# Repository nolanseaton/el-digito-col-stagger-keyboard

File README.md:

# El Digito - Col Stagger PCB and Case

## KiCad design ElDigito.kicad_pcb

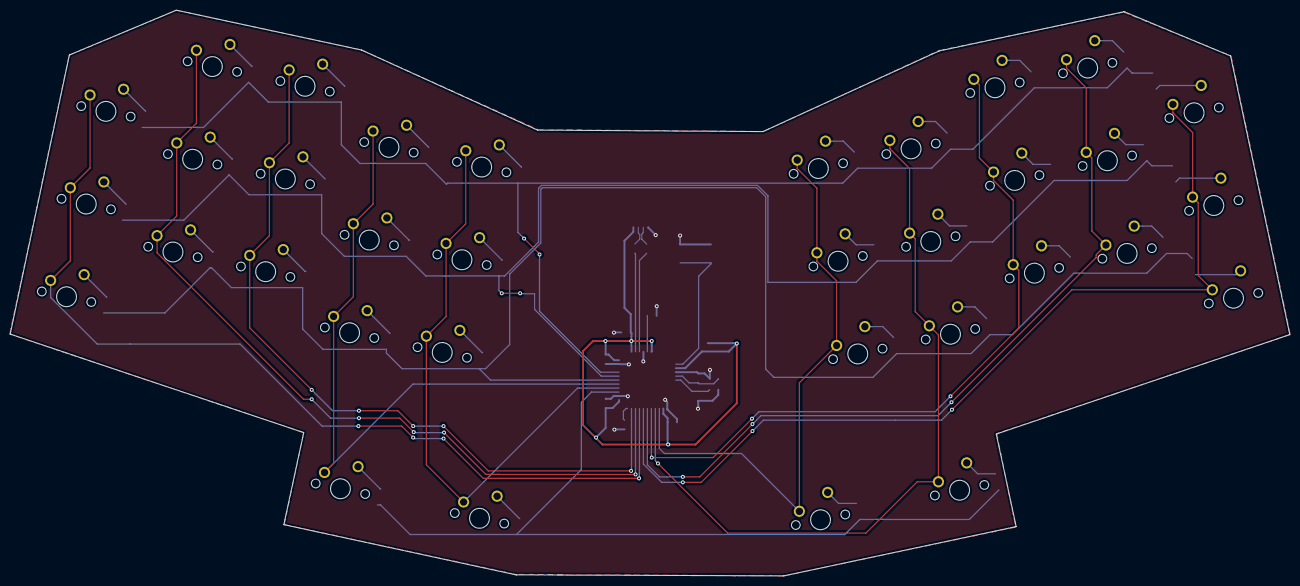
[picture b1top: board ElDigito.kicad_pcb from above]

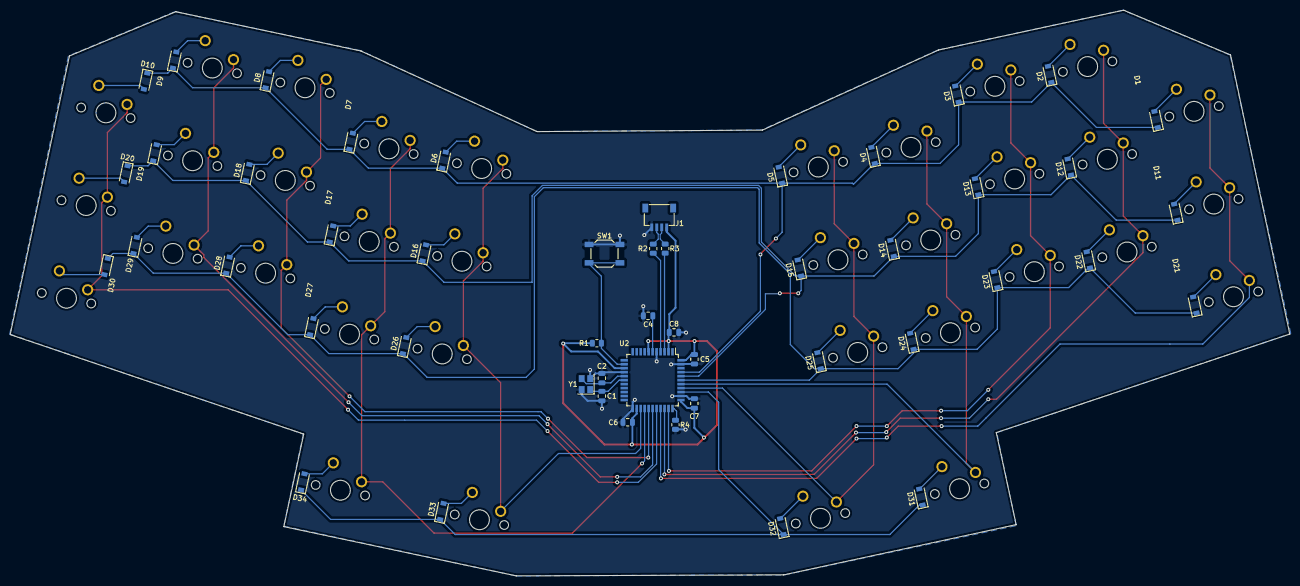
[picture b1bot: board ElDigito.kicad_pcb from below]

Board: 2 copper layers, 257.2 x 113.7 mm, 83 parts (49 on the bottom side), 59 nets.

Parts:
C1, C2: 22pF; C_0805_2012Metric
C4: 1uF; C_0805_2012Metric
C5, C6, C7: 0.1uF; C_0805_2012Metric
C8: 10uF; C_0805_2012Metric
D1, D2, D3, D4, D5, D6, D7, D8, D9, D10, D11, D12, D13, D14, D15, D16, D17, D18, D19, D20, D21, D22, D23, D24, D25, D26, D27, D28, D29, D30, D31, D32, D33, D34: D_Small; D_SOD-123
J1: Conn_01x04_Female; JST-SR-4
MX1, MX2, MX3, MX4, MX5, MX6, MX7, MX8, MX9, MX10, MX11, MX12, MX13, MX14, MX15, MX16, MX17, MX18, MX19, MX20, MX21, MX22, MX23, MX24, MX25, MX26, MX27, MX28, MX29, MX30, MX31, MX32, MX33, MX34: MX-NoLED; MXOnly-1U-NoLED
R1, R4: 10k; R_0805_2012Metric
R2, R3: 22; R_0805_2012Metric
SW1: SW_Push; SW_SPST_SKQG_WithoutStem
U2: ATmega32U4-A; TQFP-44_10x10mm_P0.8mm
Y1: 16MHz; Crystal_SMD_3225-4Pin_3.2x2.5mm

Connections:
+5V: C5.1, C6.1, C7.1, C8.1, J1.1, R1.2, U2.2 (UVCC), U2.7 (VBUS), U2.14 (VCC), U2.24 (AVCC), U2.34 (VCC), U2.44 (AVCC)
/COL0: MX1.1 (COL), MX11.1 (COL), MX21.1 (COL), U2.30 (PB6)
/COL1: MX2.1 (COL), MX12.1 (COL), MX22.1 (COL), U2.31 (PC6)
/COL2: MX3.1 (COL), MX13.1 (COL), MX23.1 (COL), U2.32 (PC7)
/COL3: MX4.1 (COL), MX14.1 (COL), MX24.1 (COL), MX31.1 (COL), U2.38 (PF5)
/COL4: MX5.1 (COL), MX15.1 (COL), MX25.1 (COL), MX32.1 (COL), U2.37 (PF6)
/COL5: MX6.1 (COL), MX16.1 (COL), MX26.1 (COL), MX33.1 (COL), U2.25 (PD4)
/COL6: MX7.1 (COL), MX17.1 (COL), MX27.1 (COL), MX34.1 (COL), U2.26 (PD6)
/COL7: MX8.1 (COL), MX18.1 (COL), MX28.1 (COL), U2.27 (PD7)
/COL8: MX9.1 (COL), MX19.1 (COL), MX29.1 (COL), U2.28 (PB4)
/COL9: MX10.1 (COL), MX20.1 (COL), MX30.1 (COL), U2.29 (PB5)
/D+: J1.3, R2.1
/D-: J1.2, R3.1
/ROW0: D1.1 (K), D2.1 (K), D3.1 (K), D4.1 (K), D5.1 (K), D6.1 (K), D7.1 (K), D8.1 (K), D9.1 (K), D10.1 (K), U2.41 (PF0)
/ROW1: D11.1 (K), D12.1 (K), D13.1 (K), D14.1 (K), D15.1 (K), D16.1 (K), D17.1 (K), D18.1 (K), D19.1 (K), D20.1 (K), U2.40 (PF1)
/ROW2: D21.1 (K), D22.1 (K), D23.1 (K), D24.1 (K), D25.1 (K), D26.1 (K), D27.1 (K), D28.1 (K), D29.1 (K), D30.1 (K), U2.39 (PF4)
/ROW3: D31.1 (K), D32.1 (K), D33.1 (K), D34.1 (K), U2.36 (PF7)
GND: C1.1, C2.1, C4.2, C5.2, C6.2, C7.2, C8.2, J1.4, R4.2, SW1.1, U2.5 (UGND), U2.15 (GND), U2.23 (GND), U2.35 (GND), U2.43 (GND), Y1.2, Y1.4
unnamed: C1.2, U2.17 (XTAL1), Y1.1
unnamed: C2.2, U2.16 (XTAL2), Y1.3
unnamed: C4.1, U2.6 (UCAP)
unnamed: D1.2 (A), MX1.2 (ROW)
unnamed: D2.2 (A), MX2.2 (ROW)
unnamed: D3.2 (A), MX3.2 (ROW)
unnamed: D4.2 (A), MX4.2 (ROW)
unnamed: D5.2 (A), MX5.2 (ROW)
unnamed: D6.2 (A), MX6.2 (ROW)
unnamed: D7.2 (A), MX7.2 (ROW)
unnamed: D8.2 (A), MX8.2 (ROW)
unnamed: D9.2 (A), MX9.2 (ROW)
unnamed: D10.2 (A), MX10.2 (ROW)
unnamed: D11.2 (A), MX11.2 (ROW)
unnamed: D12.2 (A), MX12.2 (ROW)
unnamed: D13.2 (A), MX13.2 (ROW)
unnamed: D14.2 (A), MX14.2 (ROW)
unnamed: D15.2 (A), MX15.2 (ROW)
unnamed: D16.2 (A), MX16.2 (ROW)
unnamed: D17.2 (A), MX17.2 (ROW)
unnamed: D18.2 (A), MX18.2 (ROW)
unnamed: D19.2 (A), MX19.2 (ROW)
unnamed: D20.2 (A), MX20.2 (ROW)
unnamed: D21.2 (A), MX21.2 (ROW)
unnamed: D22.2 (A), MX22.2 (ROW)
unnamed: D23.2 (A), MX23.2 (ROW)
unnamed: D24.2 (A), MX24.2 (ROW)
unnamed: D25.2 (A), MX25.2 (ROW)
unnamed: D26.2 (A), MX26.2 (ROW)
unnamed: D27.2 (A), MX27.2 (ROW)
unnamed: D28.2 (A), MX28.2 (ROW)
unnamed: D29.2 (A), MX29.2 (ROW)
unnamed: D30.2 (A), MX30.2 (ROW)
unnamed: D31.2 (A), MX31.2 (ROW)
unnamed: D32.2 (A), MX32.2 (ROW)
unnamed: D33.2 (A), MX33.2 (ROW)
unnamed: D34.2 (A), MX34.2 (ROW)
unnamed: R1.1, SW1.2, U2.13 (~RESET)
unnamed: R2.2, U2.4 (D+)
unnamed: R3.2, U2.3 (D-)
unnamed: R4.1, U2.33 (~HWB/PE2)

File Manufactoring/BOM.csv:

Ref,Qnty,Value,Cmp name,Footprint,Description
"C1, C2, ",2,22pF,C_Small,Capacitor_SMD:C_0805_2012Metric,"Unpolarized capacitor, small symbol"
"C4, ",1,1uF,C_Small,Capacitor_SMD:C_0805_2012Metric,"Unpolarized capacitor, small symbol"
"C5, C6, C7, ",3,0.1uF,C_Small,Capacitor_SMD:C_0805_2012Metric,"Unpolarized capacitor, small symbol"
"C8, ",1,10uF,C_Small,Capacitor_SMD:C_0805_2012Metric,"Unpolarized capacitor, small symbol"
"D1, D2, D3, D4, D5, D6, D7, D8, D9, D10, D11, D12, D13, D14, D15, D16, D17, D18, D19, D20, D21, D22, D23, D24, D25, D26, D27, D28, D29, D30, D31, D32, D33, D34, ",34,D_Small,D_Small,Diode_SMD:D_SOD-123,"Diode, small symbol"
"J1, ",1,Conn_01x04_Female,Conn_01x04_Female,random-keyboard-parts:JST-SR-4,"Generic connector, single row, 01x04, script generated (kicad-library-utils/schlib/autogen/connector/)"
"R1, R4, ",2,10k,R_Small,Resistor_SMD:R_0805_2012Metric,"Resistor, small symbol"
"R2, R3, ",2,22,R_Small,Resistor_SMD:R_0805_2012Metric,"Resistor, small symbol"
"SW1, ",1,SW_Push,SW_Push,Button_Switch_SMD:SW_SPST_SKQG_WithoutStem,"Push button switch, generic, two pins"
"U2, ",1,ATmega32U4-A,ATmega32U4-A,Package_QFP:TQFP-44_10x10mm_P0.8mm,"16MHz, 32kB Flash, 2.5kB SRAM, 1kB EEPROM, USB 2.0, TQFP-44"
"Y1, ",1,16MHz,Crystal_GND24_Small,Crystal:Crystal_SMD_3225-4Pin_3.2x2.5mm,"Four pin crystal, GND on pins 2 and 4, small symbol"

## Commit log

2023-02-21 Init
